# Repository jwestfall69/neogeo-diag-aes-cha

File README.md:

# neogeo-diag-aes-cha

## Overview
This is a custom NeoGeo AES CHA board that is used in conjunction with the [NeoGeo Diag Bios](https://github.com/jwestfall69/neogeo-diag-bios) that allows for testing the Z80 sound system with a custom diag M1 rom.  This doesn't allow for any new type of testing that was done previously, but make it possible to create a diag CHA board without having to sacrifice a original SNK CHA board.

The NeoGeo uses bank switching to allow full access to the M1 rom.  This is normally handled by a custom NEO-ZMC chip on the CHA board.  I ended up making 3 different boards you can choose from to deal with this bank switching:

A Board that uses a original NEO-ZMC:<br>
<br>

2 Boards that replace the NEO-ZMC with a CPLD (Socketed PLCC44 and TQFP44):<br>

Personally I would go with the NEO-ZMC based board since the NEO-ZMC is available as NOS for around $2 each.  More on this in the BOM below.  Additionally with the chip shortage its a little difficult to get the CPLDs, plus the fun of programming them.

## PCB Manufacturing
PCB should be 1.6mm thickness.  With these boards likely being inserted and removed numerous times its suggested you use ENIG surface finishing and gold fingers w/chamfering.

I've been using [jlcpcb](https://jlcpcb.com/) for PCB manufacturing.  Just watch out that by default they will add an order number to the silk screen unless you tell them not to.

## BOMs
**IMPORTANT:**

  * The 32 pin DIP sockets listed in the BOMs are special low profile ones.  Normal sockets + EPROM are to tall for the board to be able to fit behind the PROG board.
  * Stock of the CPLD is pretty low everywhere.  If you can't find them on digikey/mouser, you might be able to buy them directly from [Microchip](https://www.microchipdirect.com/).
  * If you buy a used CPLD its possible the JTAG pins were repurposed as I/O pins.  This will make it impossible to re-program with JTAG.
  * When buying the EPROMs I would advise against buying any that claimed to be new.  Sellers claiming this maybe trying to sell 
  slower speed variants re-labeled as something faster or just straight up fakes.

### NEO-ZMC based board
| Quantity | Description | Part Number | Digikey | Notes |
|:--------:|:------------|-------------|---------|-------|
| 1        | NEO-ZMC | NEO-ZMC | | NOS Availible:<br> - On [Aliexpress](https://www.aliexpress.us/item/2251832763681253.html?gatewayAdapt=glo2usa4itemAdapt)<br>- On [arcade-projects.com](https://www.arcade-projects.com/threads/openkeys-neogeo-diag-prog-boards.24392/) |
| 2        | 74HC574 pin 14 SOIC | SN74HC574NSR | [296-31816-1-ND](https://www.digikey.com/en/products/detail/texas-instruments/SN74HC574NSR/1571235) | |
| 2       | Low Profile 32pin DIP Socket | 115-93-632-41-003000 | [ED5632-ND](https://www.digikey.com/en/products/detail/mill-max-manufacturing-corp/115-93-632-41-003000/81902) | This is optional if you want just solder the eproms to the board |
| 2       | 1Mbit (128k x 8bit) 32 pin EPROM, 150ns or faster | 27C1001<br>or<br>27C010 | | |
| 5        | 100nf / 0.1uf Ceramic Capacitor 0805 Size | CL21B104KBCNNNC | [1276-1003-2-ND](https://www.digikey.com/en/products/detail/samsung-electro-mechanics/CL21B104KBCNNNC/3886661) | Any 100nf 0805 is fine |

### CPLD PLCC44 (Socket) based board
| Quantity | Description | Part Number | Digikey | Notes |
|:--------:|:------------|-------------|---------|-------|
| 1        | CLPD PLCC 44 pin | Microchip/Atmel ATF1502AS-xxJU44<br>or<br>ATF1504AS-xxJU44 | [ATF1502AS-7JX44-ND](https://www.digikey.com/en/products/detail/microchip-technology/ATF1502AS-7JX44/1027048)<br>[ATF1504AS-10JU44](https://www.digikey.com/en/products/detail/microchip-technology/ATF1504AS-10JU44/1118923) | Other speeds should work too |
| 1        | PLCC 44 pin through hole socket | | | |
| 2        | 74HC574 pin 14 SOIC | SN74HC574NSR | [296-31816-1-ND](https://www.digikey.com/en/products/detail/texas-instruments/SN74HC574NSR/1571235) | |
| 2       | Low Profile 32pin DIP Socket | 115-93-632-41-003000 | [ED5632-ND](https://www.digikey.com/en/products/detail/mill-max-manufacturing-corp/115-93-632-41-003000/81902) | This is optional if you want just solder the eproms to the board |
| 2       | 1Mbit (128k x 8bit) 32 pin EPROM, 150ns or faster | 27C1001<br>or<br>27C010 | | |
| 8       | 100nf / 0.1uf Ceramic Capacitor 0805 Size | CL21B104KBCNNNC | [1276-1003-2-ND](https://www.digikey.com/en/products/detail/samsung-electro-mechanics/CL21B104KBCNNNC/3886661) | Any 100nf 0805 is fine |

### CPLD TQFP44 based board
| Quantity | Description | Part Number | Digikey | Notes |
|:--------:|:------------|-------------|---------|-------|
| 1        | CLPD TQFP 44 pin | Microchip/Atmel ATF1502AS-xxAU44<br>or<br>ATF1504AS-xxAU44 | [ATF1502AS-10AU44](https://www.digikey.com/en/products/detail/microchip-technology/ATF1502AS-10AU44/1008375)<br>[ATF1504AS-10AU44](https://www.digikey.com/en/products/detail/microchip-technology/ATF1504AS-10AU44/1008359) | Other speeds should work too |
| 2        | 74HC574 pin 14 SOIC | SN74HC574NSR | [296-31816-1-ND](https://www.digikey.com/en/products/detail/texas-instruments/SN74HC574NSR/1571235) | |
| 2       | Low Profile 32pin DIP Socket | 115-93-632-41-003000 | [ED5632-ND](https://www.digikey.com/en/products/detail/mill-max-manufacturing-corp/115-93-632-41-003000/81902) | This is optional if you want just solder the eproms to the board |
| 2       | 1Mbit (128k x 8bit) 32 pin EPROM, 150ns or faster | 27C1001<br>or<br>27C010 | | |
| 8       | 100nf / 0.1uf Ceramic Capacitor 0805 Size | CL21B104KBCNNNC | [1276-1003-2-ND](https://www.digikey.com/en/products/detail/samsung-electro-mechanics/CL21B104KBCNNNC/3886661) | Any 100nf 0805 is fine |

## Assembly
  * Reminder from above that normal 32 pin DIP sockets will be to tall
  * On the NEO-ZMC board, take note of pin 1 location of the NEO-ZMC chip as its rotated 180 degrees from what you might expect.

## Programming the CPLD

Both CPLD based boards have a JTAG port on left side that can be used for programming the CPLD.  I've been using this [FT232H](https://www.amazon.com/dp/B07T9CPMHT?psc=1&ref=ppx_yo2ov_dt_b_product_details) based programmer along with [openocd](https://openocd.org/) software to program the CPLD.

Here is a picture of the programmer and the cable I made for it:

The programmer has pin labels on the bottom of the board.

| Programmer PIN | J-TAG PIN |
|:--------------:|:---------:|
| AD0            | TCK       |
| AD1            | TDI       |
| AD2            | TDO       |
| AD3            | TMS       |
| GND            | GND       |
| +5V            | VCC       |

I haven't done JTAG stuff before, but believe this programmer not normal in that its supplying 5V to power the CPLD, whereas I think most JTAG programmers rely on something else to supply power to the CPLD and the VCC/GND pins are just used for VCC/GND reference.

Since this programmer is supplying power, it would be powering the entire CHA board including to the EPROMS/74HC574 chips.  I haven't run into any USB over current issues doing this.  Obviously don't plug in the programmer into the CHA board if its also plugged into an AES console.

Its not necessary to solder the JTAG cable to the JTAG port on the CHA board, just insert the pins into the through hole and hold it an angle so the pins are touching the sides of the through holes like this:

As noted above I've been using openocd software for programming.  I've only used it on linux and it should be an existing package your distro.  For the following openocd commands below the location of the um232h.cfg maybe different depending on where your distro installs interface config files.  Additionally if you use a different programmer you might need to use a completely different interface config.

**Make sure the CPLD is detected**
```
# openocd -f /usr/share/openocd/scripts/interface/ftdi/um232h.cfg -c "adapter speed 400" -c "transport select jtag" -c init -c scan_chain -c shutdown

Open On-Chip Debugger 0.11.0+dev-snapshot (2023-02-14-01:09)
Licensed under GNU GPL v2
For bug reports, read
        http://openocd.org/doc/doxygen/bugs.html
adapter speed: 400 kHz

jtag
Info : clock speed 400 kHz
Warn : There are no enabled taps.  AUTO PROBING MIGHT NOT WORK!!
Info : JTAG tap: auto0.tap tap/device found: 0x0150403f (mfg: 0x01f (Atmel), part: 0x1504, ver: 0x0)
Warn : AUTO auto0.tap - use "jtag newtap auto0 tap -irlen 3 -expected-id 0x0150403f"
Warn : gdb services need one or more targets defined
   TapName             Enabled  IdCode     Expected   IrLen IrCap IrMask
-- ------------------- -------- ---------- ---------- ----- ----- ------
 0 auto0.tap              Y     0x0150403f 0x00000000     3 0x01  0x03

shutdown command invoked

```
You want to see an IdCode of 0x01504xxx or 0x01502xxx based on which CPLD you are using.

**Programming the CPLD**<br>
For programming you will need the .svf firmware file for the CPLD you are using.  In the below example I have a ATF1504AS-7AX44 TQFP CPLD, so I use the atf1504as-tqfp44.svf firmware.

```
# openocd -f /usr/share/openocd/scripts/interface/ftdi/um232h.cfg -c "adapter speed 400" -c "transport select jtag" -c init -c "svf atf1504as-tqfp44/atf1504as-tqfp44.svf" -c shutdown

Open On-Chip Debugger 0.11.0+dev-snapshot (2023-02-14-01:09)
Licensed under GNU GPL v2
For bug reports, read
        http://openocd.org/doc/doxygen/bugs.html
adapter speed: 400 kHz

jtag
Info : clock speed 400 kHz
Warn : There are no enabled taps.  AUTO PROBING MIGHT NOT WORK!!
Info : JTAG tap: auto0.tap tap/device found: 0x0150403f (mfg: 0x01f (Atmel), part: 0x1504, ver: 0x0)
Warn : AUTO auto0.tap - use "jtag newtap auto0 tap -irlen 3 -expected-id 0x0150403f"
Warn : gdb services need one or more targets defined
svf processing file: "atf1504as-tqfp44/atf1504as-tqfp44.svf"
TRST ABSENT;
ENDIR IDLE;
ENDDR IDLE;
HDR 0;
HIR 0;
TDR 0;
TIR 0;
RUNTEST 50021E-6 SEC;
STATE RESET;
STATE IDLE;
RUNTEST 50021E-6 SEC;
SIR 10 TDI (280);
SDR 10 TDI (1b9);
STATE IDLE;
SIR 10 TDI (059);
        MASK (ffffffff);
STATE IDLE;
SIR 10 TDI (2b3);
SIR 10 TDI (29e);

...

SIR 10 TDI (293);
        MASK (ffff);
STATE IDLE;
SIR 10 TDI (2a1);
SDR 11 TDI (100);
SIR 10 TDI (28c);
STATE IDLE;
RUNTEST 20001E-6 SEC;
SIR 10 TDI (291);
        MASK (ffffffff);
STATE IDLE;
SIR 10 TDI (280);
SDR 10 TDI (000);
STATE IDLE;
RUNTEST 10001E-6 SEC;
STATE RESET;
RUNTEST 50021E-6 SEC;

Time used: 0m12s393ms
svf file programmed successfully for 3299 commands with 0 errors

shutdown command invoked

```

## Programming the EPROMs
The M1 EPROM should be programmed using the diag M1 ROM provided with the neogeo diag bios.

The S1 EPROM can be programmed with most any S1 ROM from any game.  I usually just use 201-s1.s1 from mslug mame romset.

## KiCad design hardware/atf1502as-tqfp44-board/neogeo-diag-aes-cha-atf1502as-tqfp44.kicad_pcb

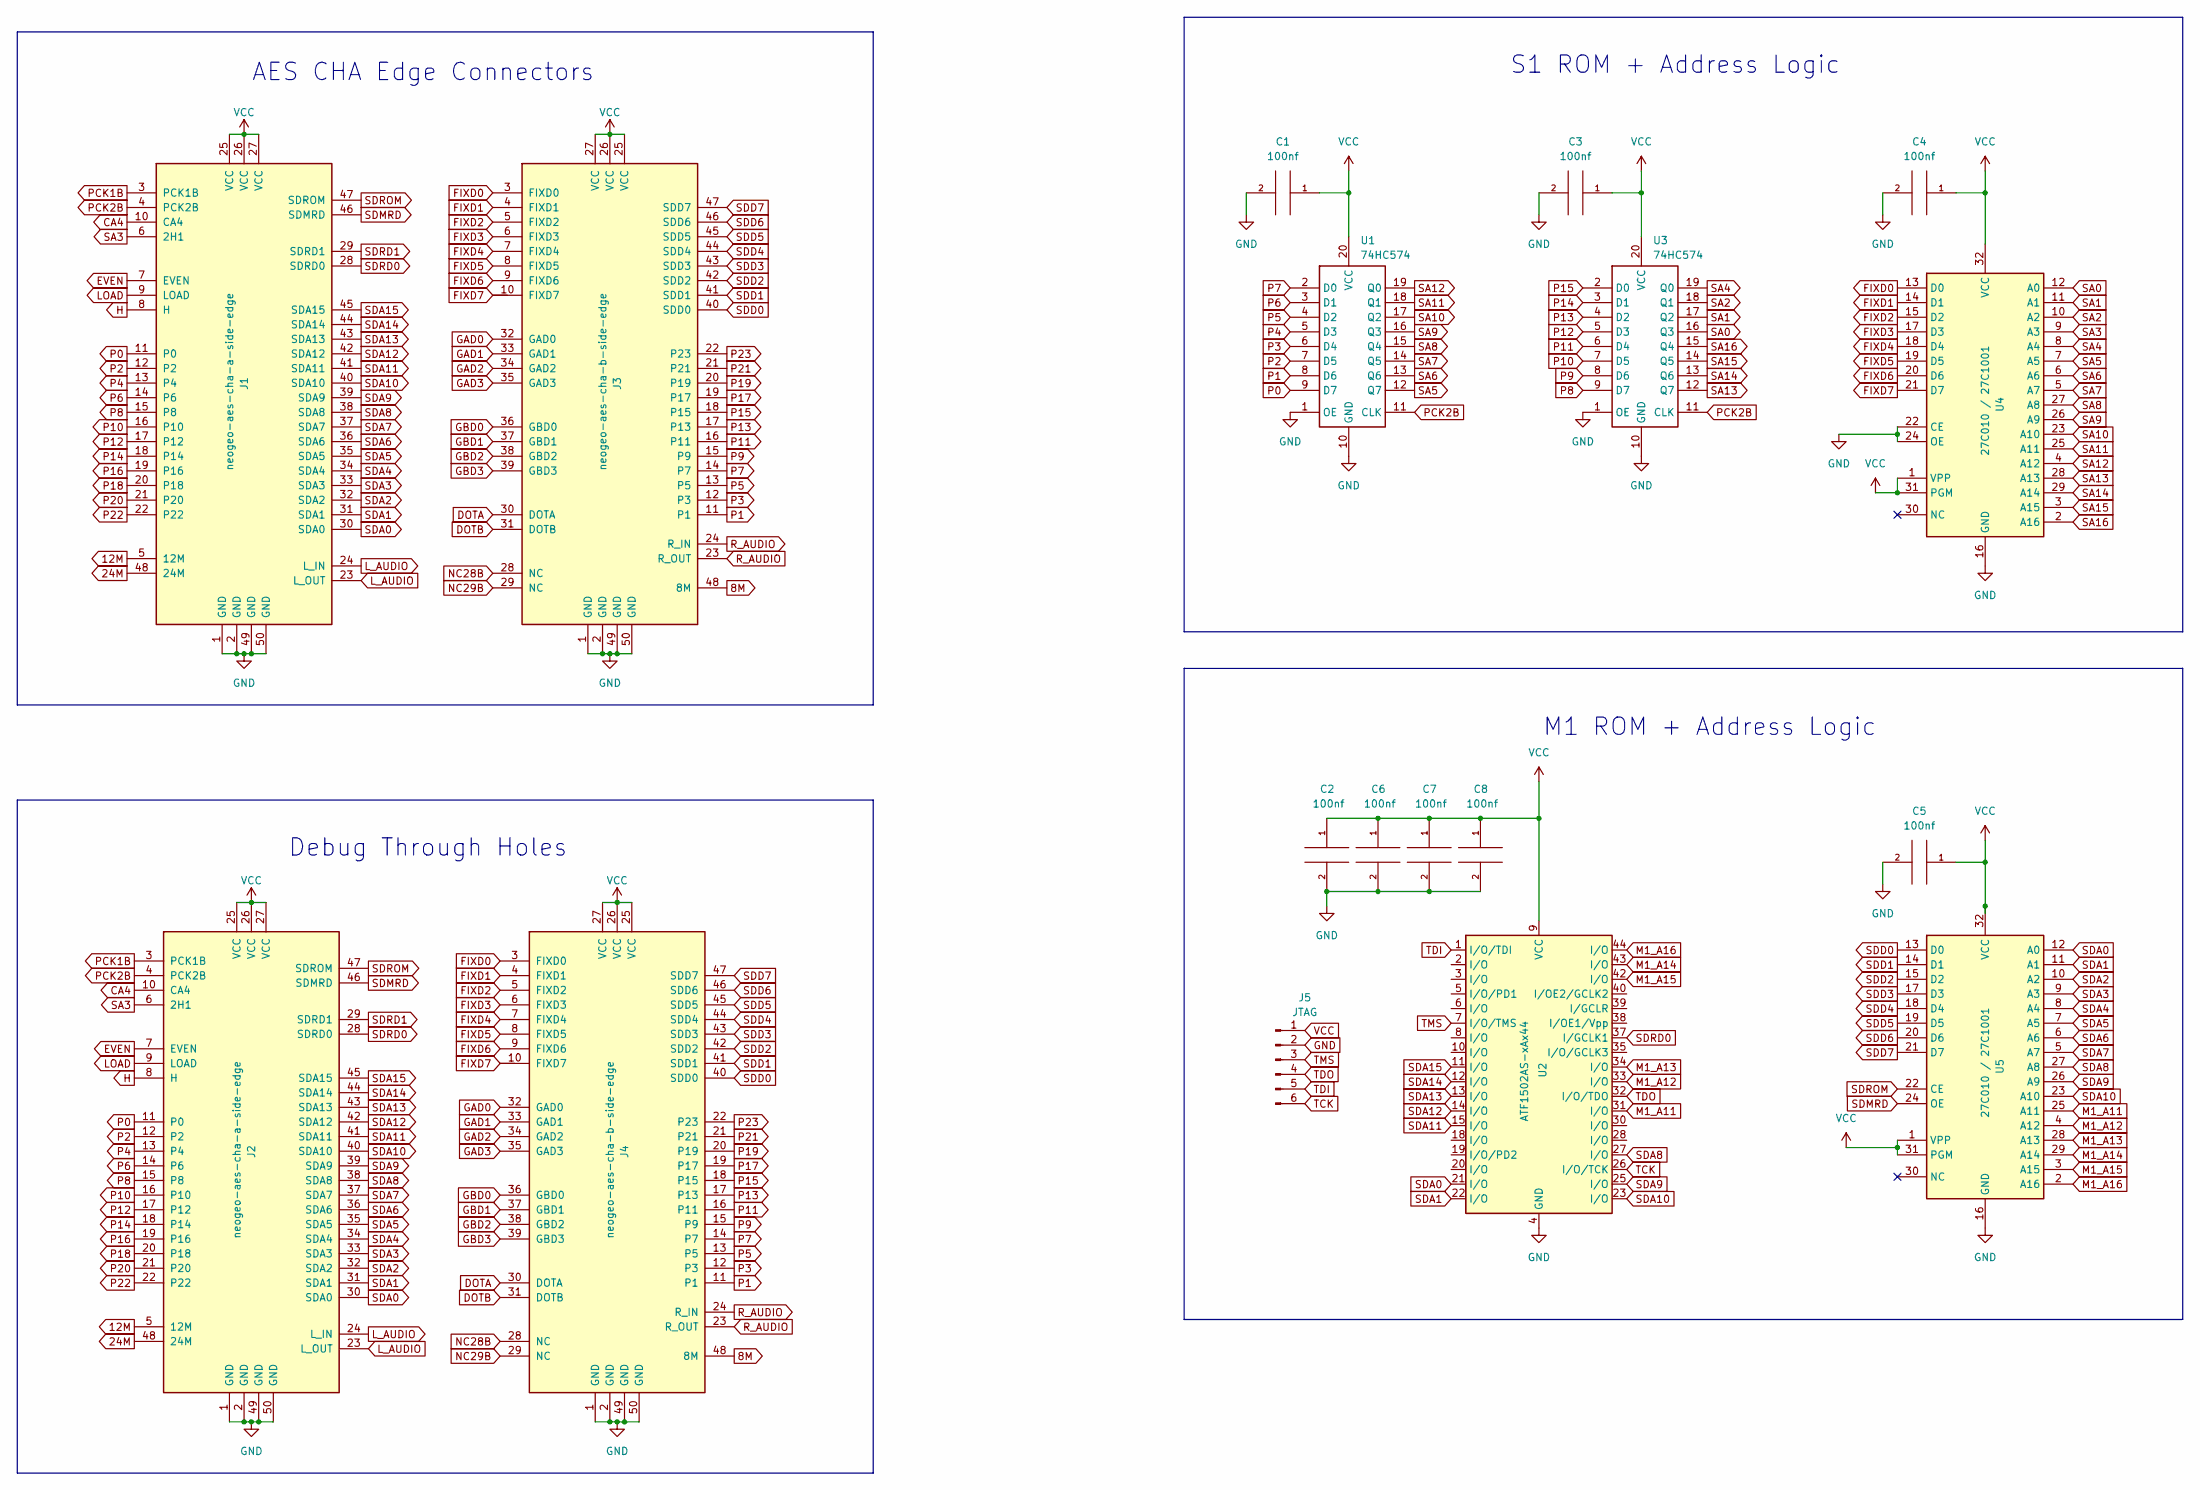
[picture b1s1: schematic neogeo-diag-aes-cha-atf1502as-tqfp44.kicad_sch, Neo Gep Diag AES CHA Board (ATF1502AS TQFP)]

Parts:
C1, C2, C3, C4, C5, C6, C7, C8: 100nf; C_0805_2012Metric
J1: neogeo-aes-cha-a-side-edge; neogeo-aes-a-side-edge
J2: neogeo-aes-cha-a-side-edge; neogeo-aes-edge-test-points
J3: neogeo-aes-cha-b-side-edge; neogeo-aes-b-side-edge
J4: neogeo-aes-cha-b-side-edge; neogeo-aes-edge-test-points
J5: JTAG; PinHeader_1x06_P2.54mm_Vertical
U1, U3: 74HC574; SO-20_5.3x12.6mm_P1.27mm
U2: ATF1502AS-xAx44; TQFP-44_10x10mm_P0.8mm
U4, U5: 27C010 / 27C1001; DIP-32_W15.24mm_Socket_LongPads

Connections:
8M: J3.48 (8M), J4.48 (8M)
12M: J1.5 (12M), J2.5 (12M)
24M: J1.48 (24M), J2.48 (24M)
CA4: J1.10 (CA4), J2.10 (CA4)
DOTA: J3.30 (DOTA), J4.30 (DOTA)
DOTB: J3.31 (DOTB), J4.31 (DOTB)
EVEN: J1.7 (EVEN), J2.7 (EVEN)
FIXD0: J3.3 (FIXD0), J4.3 (FIXD0), U4.13 (D0)
FIXD1: J3.4 (FIXD1), J4.4 (FIXD1), U4.14 (D1)
FIXD2: J3.5 (FIXD2), J4.5 (FIXD2), U4.15 (D2)
FIXD3: J3.6 (FIXD3), J4.6 (FIXD3), U4.17 (D3)
FIXD4: J3.7 (FIXD4), J4.7 (FIXD4), U4.18 (D4)
FIXD5: J3.8 (FIXD5), J4.8 (FIXD5), U4.19 (D5)
FIXD6: J3.9 (FIXD6), J4.9 (FIXD6), U4.20 (D6)
FIXD7: J3., J3.10 (FIXD7), J4., J4.10 (FIXD7), U4.21 (D7)
GAD0: J3.32 (GAD0), J4.32 (GAD0)
GAD1: J3.33 (GAD1), J4.33 (GAD1)
GAD2: J3.34 (GAD2), J4.34 (GAD2)
GAD3: J3.35 (GAD3), J4.35 (GAD3)
GBD0: J3.36 (GBD0), J4.36 (GBD0)
GBD1: J3.37 (GBD1), J4.37 (GBD1)
GBD2: J3.38 (GBD2), J4.38 (GBD2)
GBD3: J3.39 (GBD3), J4.39 (GBD3)
GND: C1.2, C2.2, C3.2, C4.2, C5.2, C6.2, C7.2, C8.2, J1.1 (GND), J1.2 (GND), J1.49 (GND), J1.50 (GND), J2.1 (GND), J2.2 (GND), J2.49 (GND), J2.50 (GND), J3.1 (GND), J3.2 (GND), J3.49 (GND), J3.50 (GND), J4.1 (GND), J4.2 (GND), J4.49 (GND), J4.50 (GND), J5.2, U1.1 (OE), U1.10 (GND), U2.4 (GND), U2.16 (GND), U2.24 (GND), U2.36 (GND), U3.1 (OE), U3.10 (GND), U4.16 (GND), U4.22 (CE), U4.24 (OE), U5.16 (GND)
H: J1.8 (H), J2.8 (H)
LOAD: J1.9 (LOAD), J2.9 (LOAD)
L_AUDIO: J1.23 (L_OUT), J1.24 (L_IN), J2.23 (L_OUT), J2.24 (L_IN)
M1_A11: U2.31 (I/O), U5.25 (A11)
M1_A12: U2.33 (I/O), U5.4 (A12)
M1_A13: U2.34 (I/O), U5.28 (A13)
M1_A14: U2.43 (I/O), U5.29 (A14)
M1_A15: U2.42 (I/O), U5.3 (A15)
M1_A16: U2.44 (I/O), U5.2 (A16)
NC28B: J3.28 (NC), J4.28 (NC)
NC29B: J3.29 (NC), J4.29 (NC)
P0: J1.11 (P0), J2.11 (P0), U1.9 (D7)
P1: J3.11 (P1), J4.11 (P1), U1.8 (D6)
P2: J1.12 (P2), J2.12 (P2), U1.7 (D5)
P3: J3.12 (P3), J4.12 (P3), U1.6 (D4)
P4: J1.13 (P4), J2.13 (P4), U1.5 (D3)
P5: J3.13 (P5), J4.13 (P5), U1.4 (D2)
P6: J1.14 (P6), J2.14 (P6), U1.3 (D1)
P7: J3.14 (P7), J4.14 (P7), U1.2 (D0)
P8: J1.15 (P8), J2.15 (P8), U3.9 (D7)
P9: J3.15 (P9), J4.15 (P9), U3.8 (D6)
P10: J1.16 (P10), J2.16 (P10), U3.7 (D5)
P11: J3.16 (P11), J4.16 (P11), U3.6 (D4)
P12: J1.17 (P12), J2.17 (P12), U3.5 (D3)
P13: J3.17 (P13), J4.17 (P13), U3.4 (D2)
P14: J1.18 (P14), J2.18 (P14), U3.3 (D1)
P15: J3.18 (P15), J4.18 (P15), U3.2 (D0)
P16: J1.19 (P16), J2.19 (P16)
P17: J3.19 (P17), J4.19 (P17)
P18: J1.20 (P18), J2.20 (P18)
P19: J3.20 (P19), J4.20 (P19)
P20: J1.21 (P20), J2.21 (P20)
P21: J3.21, J4.21
P22: J1.22, J2.22
P23: J3.22 (P23), J4.22 (P23)
PCK1B: J1.3 (PCK1B), J2.3 (PCK1B)
PCK2B: J1.4 (PCK2B), J2.4 (PCK2B), U1.11 (CLK), U3.11 (CLK)
R_AUDIO: J3.23 (R_OUT), J3.24 (R_IN), J4.23 (R_OUT), J4.24 (R_IN)
SA0: U3.16 (Q3), U4.12 (A0)
SA1: U3.17 (Q2), U4.11 (A1)
SA2: U3.18 (Q1), U4.10 (A2)
SA3: J1.6 (2H1), J2.6 (2H1), U4.9 (A3)
SA4: U3.19 (Q0), U4.8 (A4)
SA5: U1.12 (Q7), U4.7 (A5)
SA6: U1.13 (Q6), U4.6 (A6)
SA7: U1.14 (Q5), U4.5 (A7)
SA8: U1.15 (Q4), U4.27 (A8)
SA9: U1.16 (Q3), U4.26 (A9)
SA10: U1.17 (Q2), U4.23 (A10)
SA11: U1.18 (Q1), U4.25 (A11)
SA12: U1.19 (Q0), U4.4 (A12)
SA13: U3.12 (Q7), U4.28 (A13)
SA14: U3.13 (Q6), U4.29 (A14)
SA15: U3.14 (Q5), U4.3 (A15)
SA16: U3.15 (Q4), U4.2 (A16)
SDA0: J1.30 (SDA0), J2.30 (SDA0), U2.21 (I/O), U5.12 (A0)
SDA1: J1.31 (SDA1), J2.31 (SDA1), U2.22 (I/O), U5.11 (A1)
SDA2: J1.32 (SDA2), J2.32 (SDA2), U5.10 (A2)
SDA3: J1.33 (SDA3), J2.33 (SDA3), U5.9 (A3)
SDA4: J1.34 (SDA4), J2.34 (SDA4), U5.8 (A4)
SDA5: J1.35 (SDA5), J2.35 (SDA5), U5.7 (A5)
SDA6: J1.36 (SDA6), J2.36 (SDA6), U5.6 (A6)
SDA7: J1.37 (SDA7), J2.37 (SDA7), U5.5 (A7)
SDA8: J1.38 (SDA8), J2.38 (SDA8), U2.27 (I/O), U5.27 (A8)
SDA9: J1.39 (SDA9), J2.39 (SDA9), U2.25 (I/O), U5.26 (A9)
SDA10: J1.40 (SDA10), J2.40 (SDA10), U2.23 (I/O), U5.23 (A10)
SDA11: J1.41 (SDA11), J2.41 (SDA11), U2.15 (I/O)
SDA12: J1.42 (SDA12), J2.42 (SDA12), U2.14 (I/O)
SDA13: J1.43 (SDA13), J2.43 (SDA13), U2.13 (I/O)
SDA14: J1.44 (SDA14), J2.44 (SDA14), U2.12 (I/O)
SDA15: J1.45 (SDA15), J2.45 (SDA15), U2.11 (I/O)
SDD0: J3.40 (SDD0), J4.40 (SDD0), U5.13 (D0)
SDD1: J3.41 (SDD1), J4.41 (SDD1), U5.14 (D1)
SDD2: J3.42 (SDD2), J4.42 (SDD2), U5.15 (D2)
SDD3: J3.43 (SDD3), J4.43 (SDD3), U5.17 (D3)
SDD4: J3.44 (SDD4), J4.44 (SDD4), U5.18 (D4)
SDD5: J3.45 (SDD5), J4.45 (SDD5), U5.19 (D5)
SDD6: J3.46 (SDD6), J4.46 (SDD6), U5.20 (D6)
SDD7: J3.47 (SDD7), J4.47 (SDD7), U5.21 (D7)
SDMRD: J1.46 (SDMRD), J2.46 (SDMRD), U5.24 (OE)
SDRD0: J1.28 (SDRD0), J2.28 (SDRD0), U2.37 (I/GCLK1)
SDRD1: J1.29 (SDRD1), J2.29 (SDRD1)
SDROM: J1.47 (SDROM), J2.47 (SDROM), U5.22 (CE)
TCK: J5.6, U2.26 (I/O/TCK)
TDI: J5.5, U2.1 (I/O/TDI)
TDO: J5.4, U2.32 (I/O/TDO)
TMS: J5.3, U2.7 (I/O/TMS)
VCC: C1.1, C2.1, C3.1, C4.1, C5.1, C6.1, C7.1, C8.1, J1.25 (VCC), J1.26 (VCC), J1.27 (VCC), J2.25 (VCC), J2.26 (VCC), J2.27 (VCC), J3.25 (VCC), J3.26 (VCC), J3.27 (VCC), J4.25 (VCC), J4.26 (VCC), J4.27 (VCC), J5.1, U1.20 (VCC), U2.9 (VCC), U2.17 (VCC), U2.29 (VCC), U2.41 (VCC), U3.20 (VCC), U4.1 (VPP), U4.31 (PGM), U4.32 (VCC), U5.1 (VPP), U5.31 (PGM), U5.32 (VCC)

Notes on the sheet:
S1 ROM + Address Logic
M1 ROM + Address Logic
Debug Through Holes
AES CHA Edge Connectors

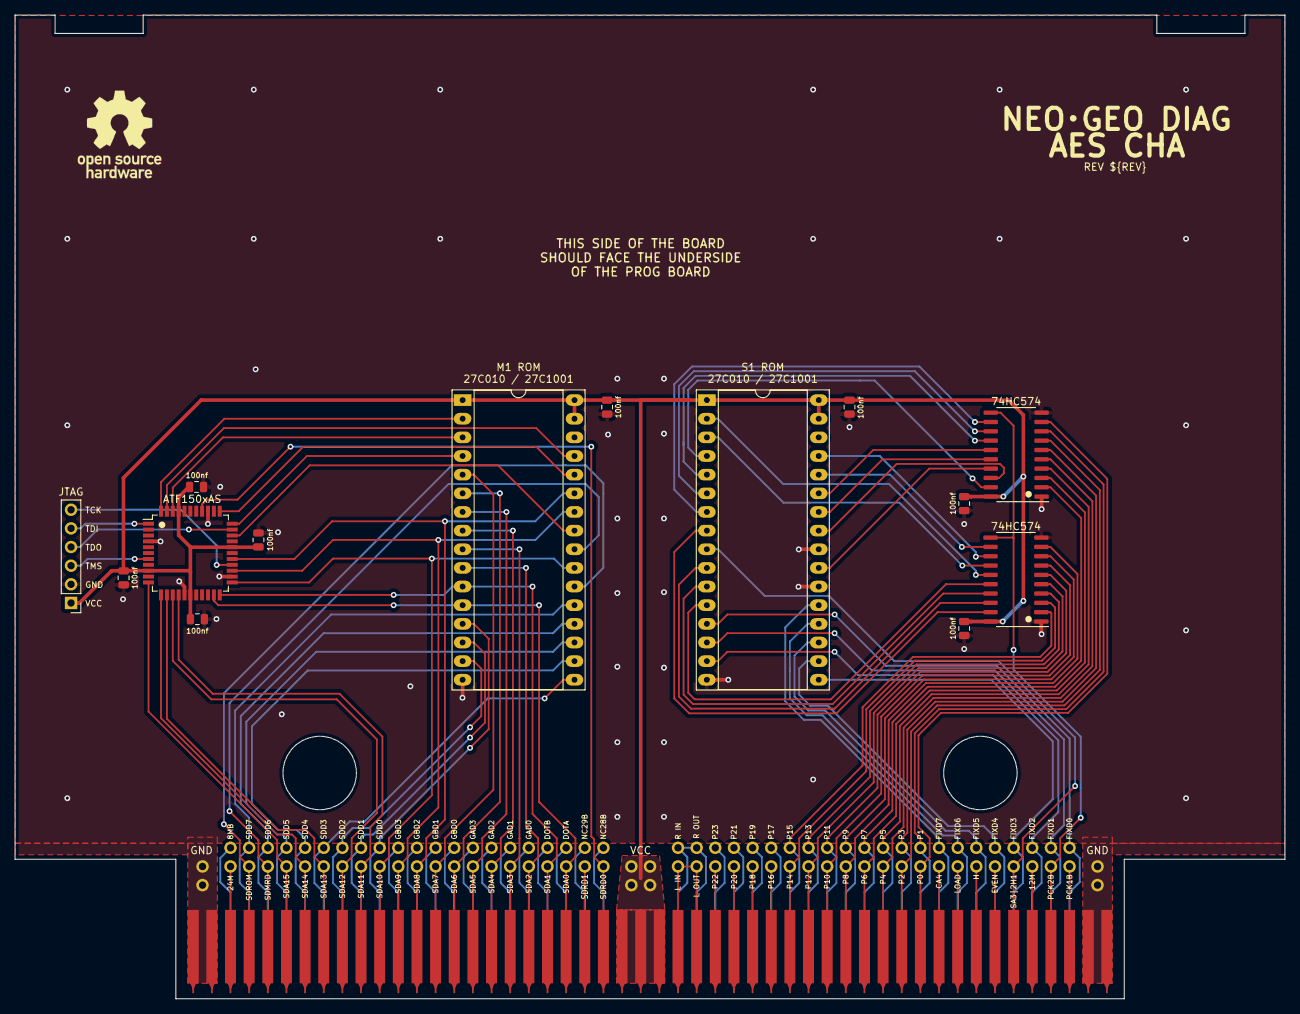
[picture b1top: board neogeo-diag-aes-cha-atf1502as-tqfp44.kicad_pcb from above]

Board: 2 copper layers, 173.0 x 134.0 mm, 18 parts (1 on the bottom side), 112 nets.

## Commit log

2023-08-17 Skeleton
2023-08-17 Add neo-zmc based board
2023-08-19 Add tf1502as plcc44 board
2023-08-19 Add atf1502as tqfp44 board
2023-08-19 Add firmwares (same as mvs version)
2023-08-20 Minor tweaks, Bump revision number on all boards so they are the same
2023-08-28 Add silkscreen to indicate pin 1 on tqfp board
2023-08-29 Add docs
